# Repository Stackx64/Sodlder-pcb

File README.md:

# Gangar-solder-pcb

An Pokemon theme  PCB designed by **Hemanta Sapkota**, made with KiCad.

The front has 6 LEDs paired with resistors including a switch, which are powered by battery cells. And there is a Spider on the front as my love for superheroes. Talking about the back, there is a cool-looking skeleton showcasing my interest towards anime .

## Schematic

## PCB Layout

## 3D View

## How to open

1. Install [KiCad](https://www.kicad.org/download/).
2. Download or clone this repository.
3. Open `(stackx).kicad_pro` in KiCad.

## About

Made with love by **Stackx64** for solder workshop.

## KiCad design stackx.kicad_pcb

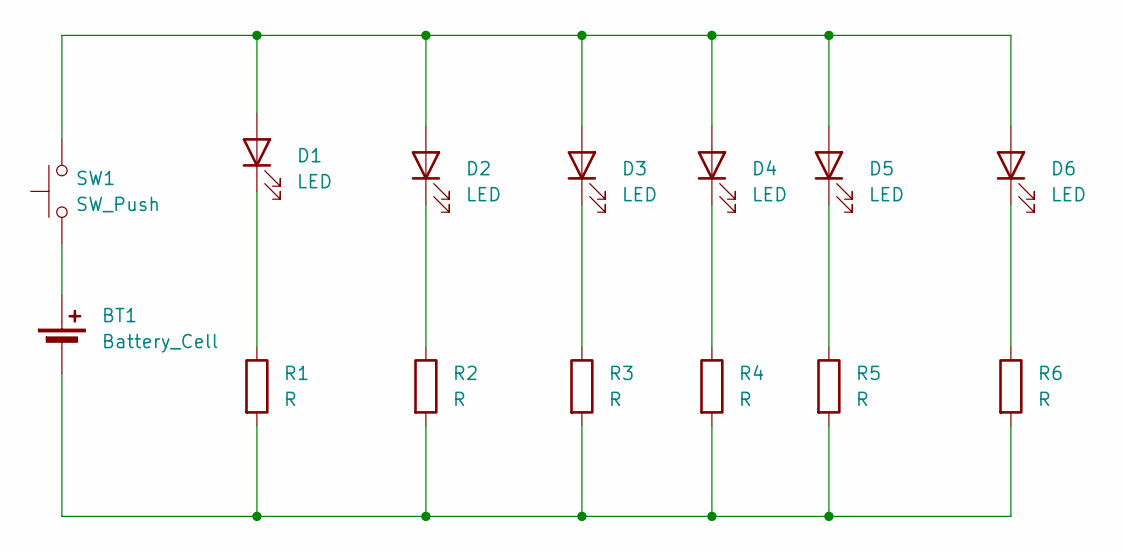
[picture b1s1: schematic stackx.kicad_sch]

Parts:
BT1: Battery_Cell; BatteryHolder_Keystone_3034_1x20mm
D1, D2, D3, D4, D5, D6: LED; LED_D5.0mm
R1, R2, R3, R4, R5, R6: R; R_Axial_DIN0207_L6.3mm_D2.5mm_P7.62mm_Horizontal
SW1: SW_Push; SW_PUSH_6mm

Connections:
unnamed: BT1.1 (+), SW1.1
unnamed: BT1.2 (-), R1.2, R2.2, R3.2, R4.2, R5.2, R6.2
unnamed: D1.2 (A), D2.2 (A), D3.2 (A), D4.2 (A), D5.2 (A), D6.2 (A), SW1.2
unnamed: D1.1 (K), R1.1
unnamed: D2.1 (K), R2.1
unnamed: D3.1 (K), R3.1
unnamed: D4.1 (K), R4.1
unnamed: D5.1 (K), R5.1
unnamed: D6.1 (K), R6.1

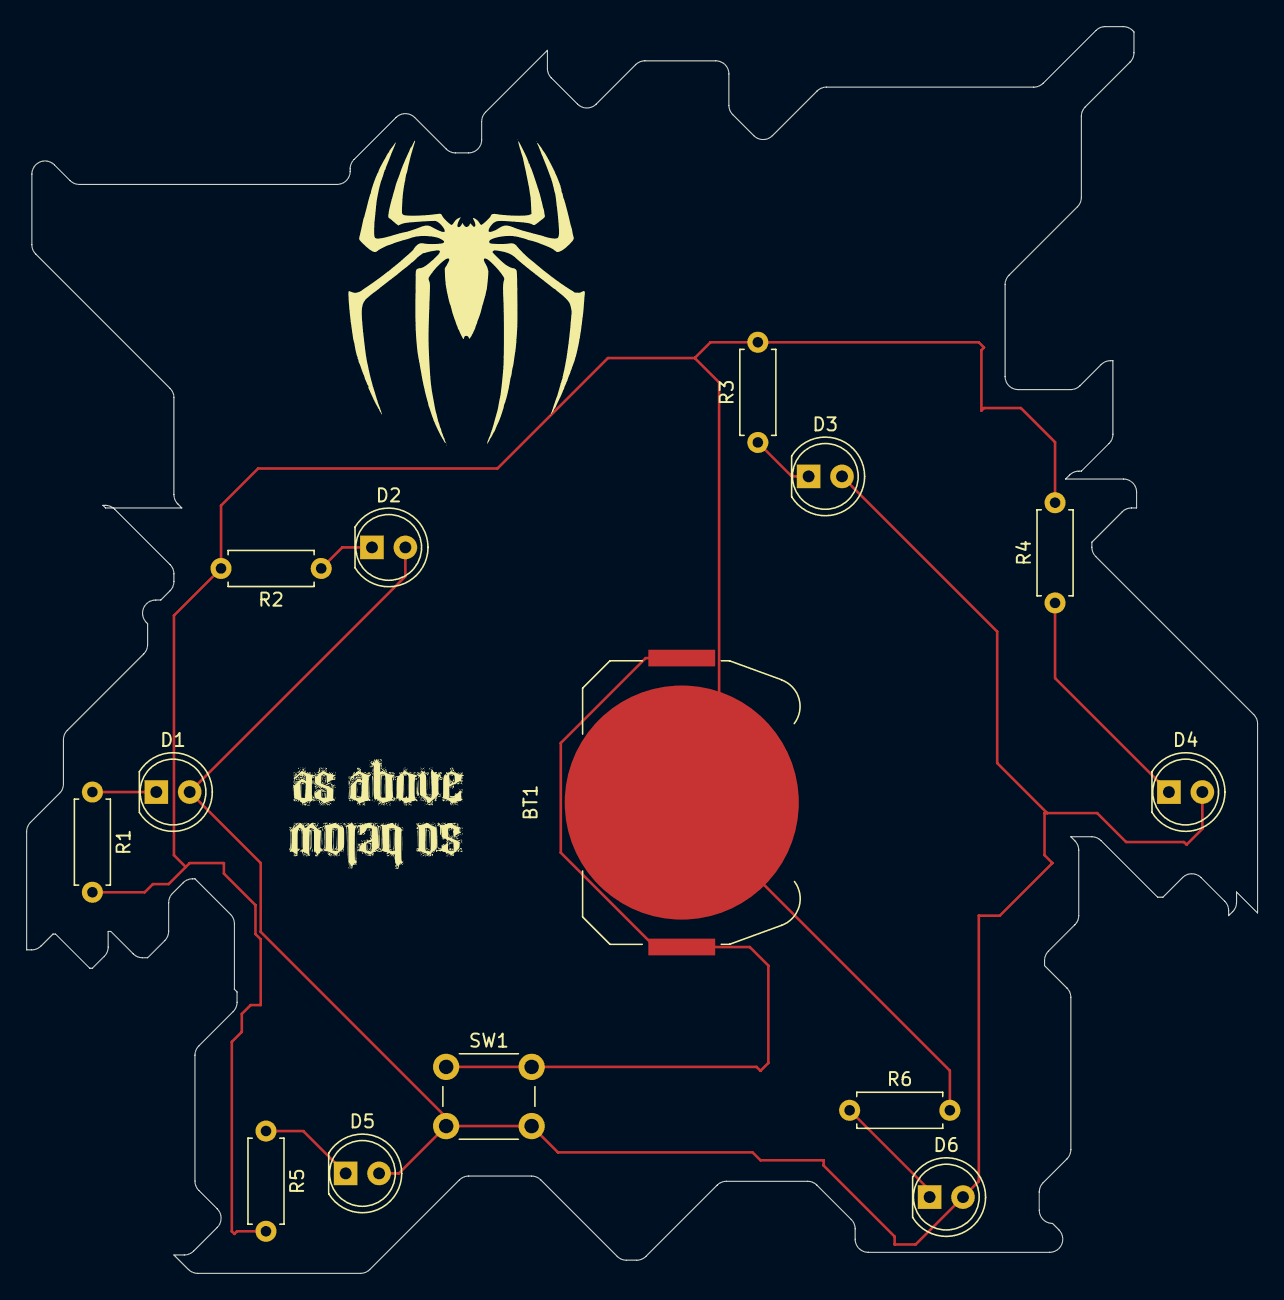
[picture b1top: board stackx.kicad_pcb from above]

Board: 2 copper layers, 93.6 x 94.8 mm, 14 parts (0 on the bottom side), 9 nets.
